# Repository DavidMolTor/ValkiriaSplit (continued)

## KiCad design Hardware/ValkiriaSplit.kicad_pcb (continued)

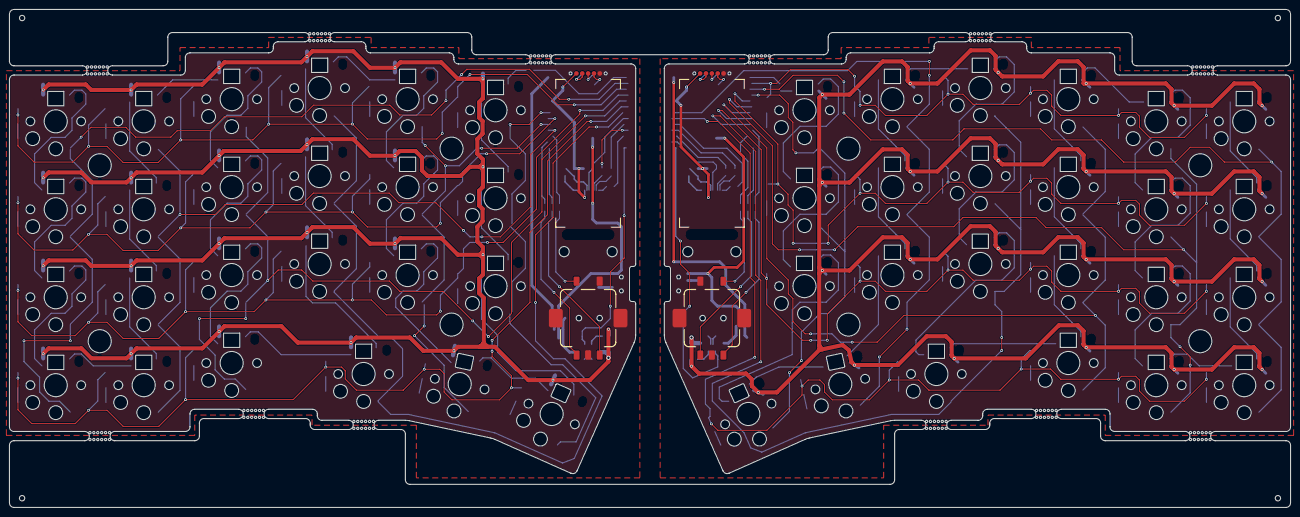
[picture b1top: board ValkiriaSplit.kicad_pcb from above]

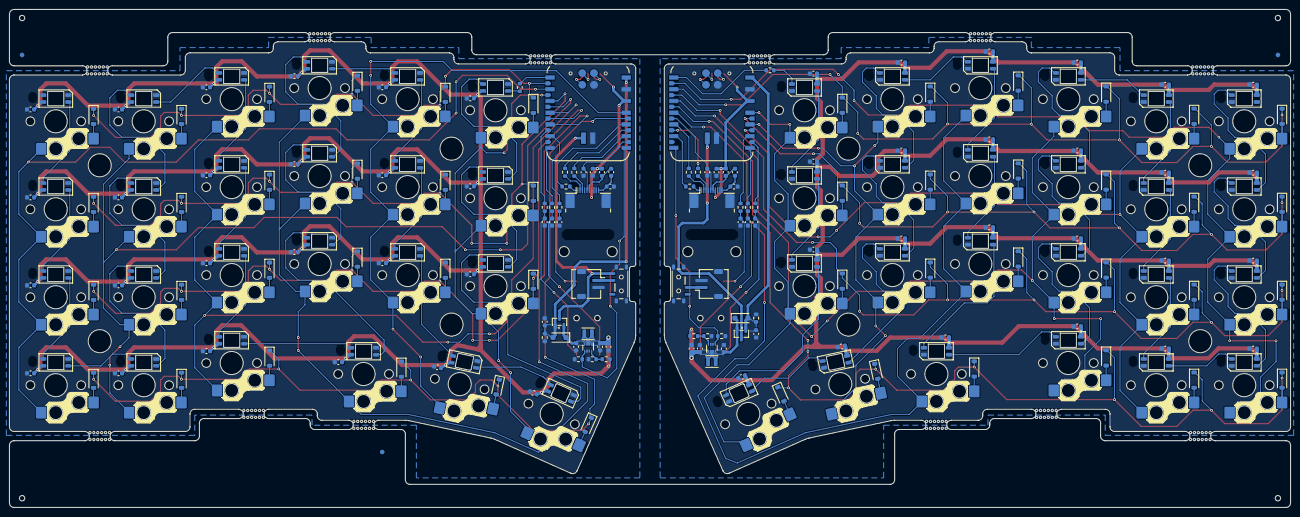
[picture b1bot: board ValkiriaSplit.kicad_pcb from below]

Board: 2 copper layers, 277.5 x 107.9 mm, 269 parts (213 on the bottom side), 175 nets.
